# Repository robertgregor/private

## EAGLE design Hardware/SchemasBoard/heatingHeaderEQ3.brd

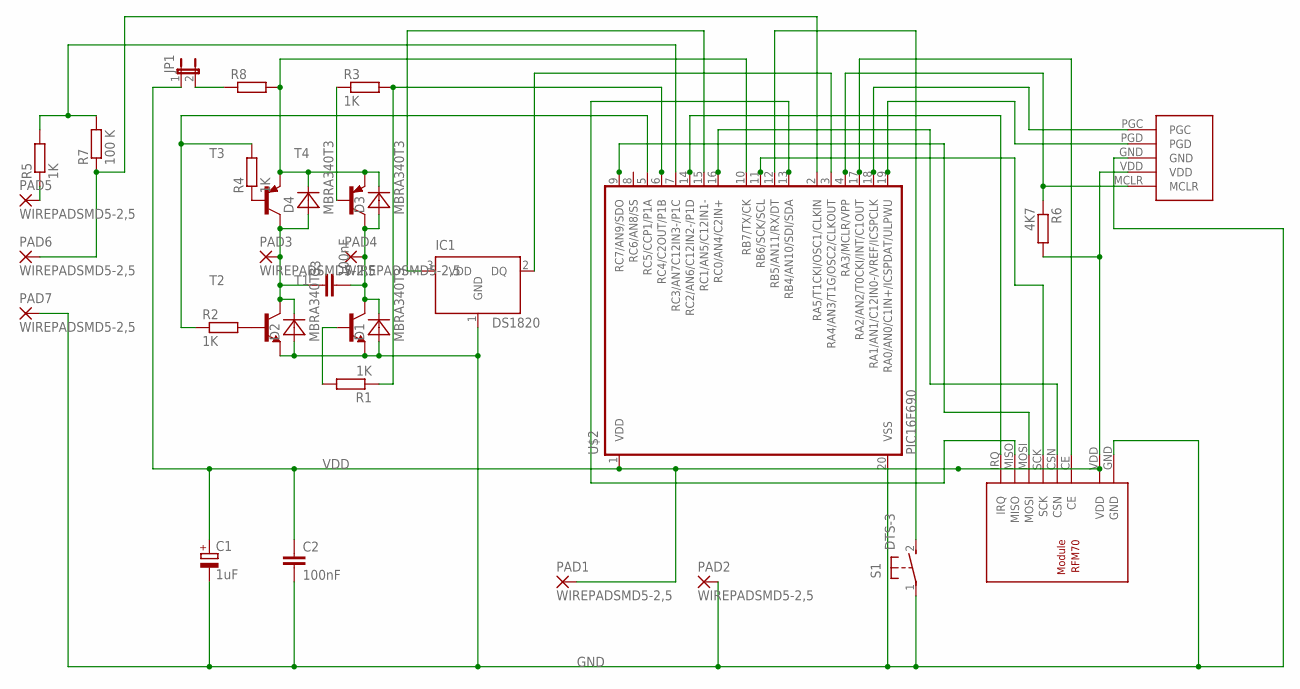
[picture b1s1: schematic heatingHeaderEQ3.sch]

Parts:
C1: 1uF; SMC_A
C2, C3: 100nF; C2012
D1, D2, D3, D4: MBRA340T3; SMA
IC1: DS1820; TO-92
JP1: JP1E; JP1
PAD1, PAD2, PAD3, PAD4, PAD5, PAD6, PAD7: WIREPADSMD5-2,5; 5-2,5
R1, R2, R3, R4, R5: 1K; R1206
R6: 4K7; R1206W
R7: 100 K; R1206
R8: R-EU_R2512W; R2512W
S1: DTS-3
T1, T2: BC817-40-NPN-SOT23-BEC; SOT23-BEC
T3, T4: BC807-16-PNP-SOT23-BEC; SOT23-BEC
U$1: RFM70
U$2: PIC16F690; SSOP20
U$3: PROGRAMMINGHEADERDIP; PROGHEADER

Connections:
GND: C1.-, C2.2, D1.A, D2.A, IC1.1 (GND), PAD2.1, PAD7.1, S1.1, T1.E, T2.E, U$1.GND, U$2.20 (VSS), U$3.GND
unnamed: IC1.2 (DQ), U$2.3 (RA4/AN3/T1G/OSC2/CLKOUT)
unnamed: JP1.2, R8.1
unnamed: IC1.3 (VDD), U$2.15 (RC1/AN5/C12IN1-)
unnamed: PAD5.1, R5.1
unnamed: U$1.MISO, U$2.13 (RB4/AN10/SDI/SDA)
unnamed: C3.1, D2.C, D4.A, PAD3.1, T2.C, T3.C
unnamed: C3.2, D1.C, D3.A, PAD4.1, T1.C, T4.C
unnamed: PAD6.1, R7.1, U$2.2 (RA5/T1CKI/OSC1/CLKIN)
unnamed: S1.2, U$2.12 (RB5/AN11/RX/DT)
unnamed: R5.2, R7.2, U$2.7 (RC3/AN7C12IN3-/P1C)
unnamed: R2.2, T2.B
unnamed: R4.1, T3.B
unnamed: D3.C, D4.C, R8.2, T3.E, T4.E, U$2.10 (RB7/TX/CK)
unnamed: U$1.CE, U$2.17 (RA2/AN2/T0CKI/INT/C1OUT)
unnamed: U$2.19 (RA0/AN0/C1IN+/ICSPDAT/ULPWU), U$3.PGD
unnamed: U$2.18 (RA1/AN1/C12IN0-/VREF/ICSPCLK), U$3.PGC
unnamed: U$1.CSN, U$2.16 (RC0/AN4/C2IN+)
unnamed: U$1.IRQ, U$2.14 (RC2/AN6/C12IN2-/P1D)
unnamed: U$1.SCK, U$2.11 (RB6/SCK/SCL)
unnamed: U$1.MOSI, U$2.9 (RC7/AN9/SDO)
unnamed: R1.2, T1.B
unnamed: R6.1, U$2.4 (RA3/MCLR/VPP), U$3.MCLR
unnamed: R3.1, T4.B
unnamed: R1.1, R3.2, U$2.6 (RC4/C2OUT/P1B)
unnamed: R2.1, R4.2, U$2.5 (RC5/CCP1/P1A)
VDD: C1.+, C2.1, JP1.1, PAD1.1, R6.2, U$1.VDD, U$2.1 (VDD), U$3.VDD

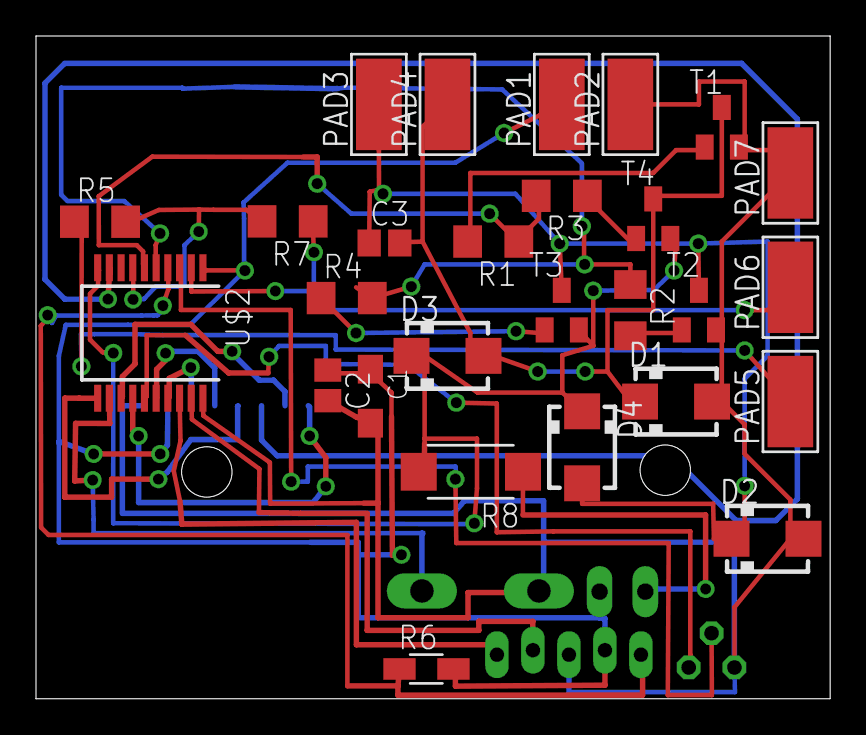
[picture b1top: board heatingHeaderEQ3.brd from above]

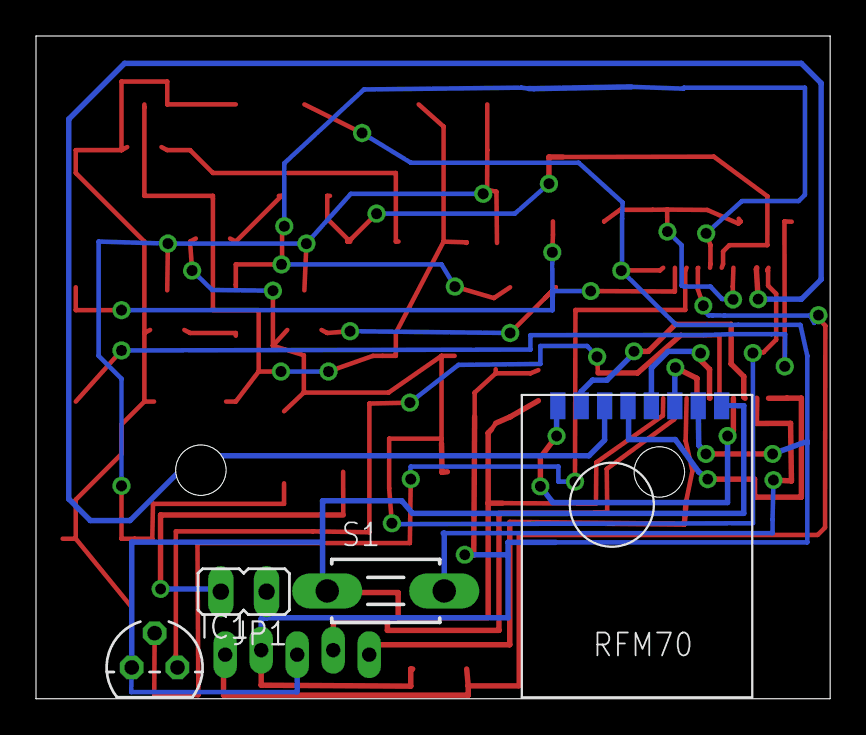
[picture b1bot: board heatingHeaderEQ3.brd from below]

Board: 2 copper layers, 44.1 x 36.8 mm, 32 parts (5 on the bottom side), 27 nets.

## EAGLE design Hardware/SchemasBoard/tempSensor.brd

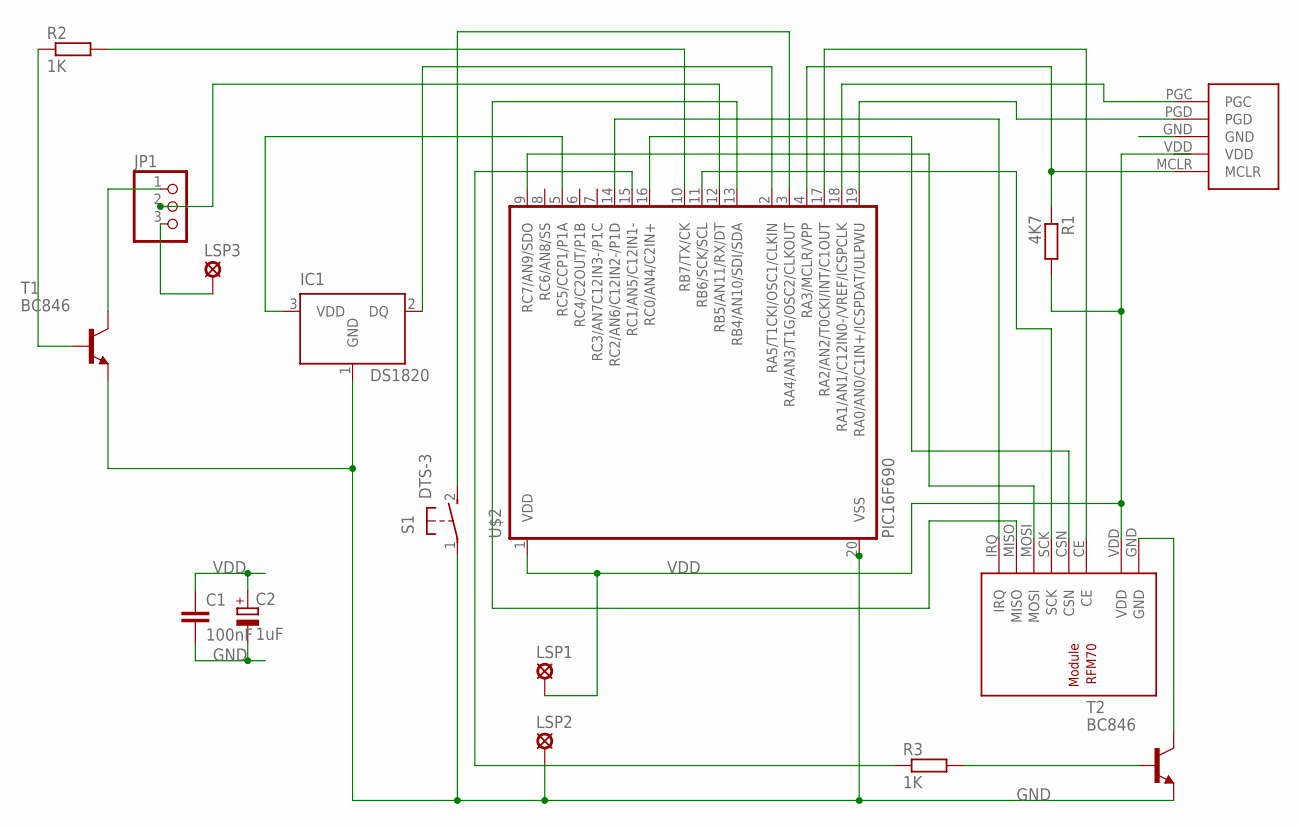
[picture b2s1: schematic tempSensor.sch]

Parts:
C1: 100nF; C2012
C2: 1uF; SMC_A
IC1: DS1820; TO-92
JP1: PINHD-1X3; 1X03
LSP1, LSP2, LSP3: SE14
R1: 4K7; R1206W
R2, R3: 1K; R1206W
S1: DTS-3
T1, T2: BC846; SOT23
U$1: RFM70
U$2: PIC16F690; SSOP20
U$3: PROGRAMMINGHEADERDIP; PROGHEADER

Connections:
GND: C1.2, C2.-, IC1.1 (GND), LSP2.MP, S1.1, T1.2 (E), T2.2 (E), U$2.20 (VSS)
unnamed: IC1.2 (DQ), U$2.2 (RA5/T1CKI/OSC1/CLKIN)
unnamed: S1.2, U$2.3 (RA4/AN3/T1G/OSC2/CLKOUT)
unnamed: IC1.3 (VDD), U$2.5 (RC5/CCP1/P1A)
unnamed: JP1.2, U$2.12 (RB5/AN11/RX/DT)
unnamed: JP1.3, LSP3.MP
unnamed: R2.2, U$2.10 (RB7/TX/CK)
unnamed: R2.1, T1.1 (B)
unnamed: U$2.19 (RA0/AN0/C1IN+/ICSPDAT/ULPWU), U$3.PGD
unnamed: JP1.1, T1.3 (C)
unnamed: U$2.18 (RA1/AN1/C12IN0-/VREF/ICSPCLK), U$3.PGC
unnamed: U$1.MISO, U$2.13 (RB4/AN10/SDI/SDA)
unnamed: T2.3 (C), U$1.GND
unnamed: R3.2, T2.1 (B)
unnamed: R3.1, U$2.15 (RC1/AN5/C12IN1-)
unnamed: U$1.CE, U$2.17 (RA2/AN2/T0CKI/INT/C1OUT)
unnamed: U$1.CSN, U$2.16 (RC0/AN4/C2IN+)
unnamed: U$1.IRQ, U$2.14 (RC2/AN6/C12IN2-/P1D)
unnamed: U$1.SCK, U$2.11 (RB6/SCK/SCL)
unnamed: U$1.MOSI, U$2.9 (RC7/AN9/SDO)
unnamed: R1.1, U$2.4 (RA3/MCLR/VPP), U$3.MCLR
VDD: C1.1, C2.+, LSP1.MP, R1.2, U$1.VDD, U$2.1 (VDD), U$3.VDD

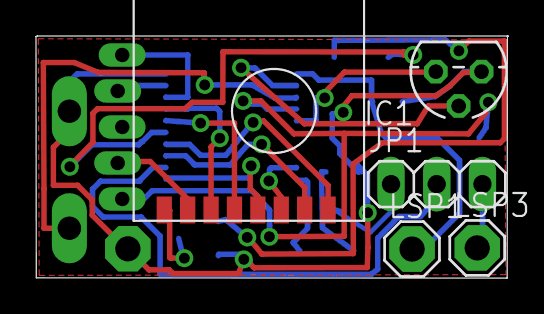
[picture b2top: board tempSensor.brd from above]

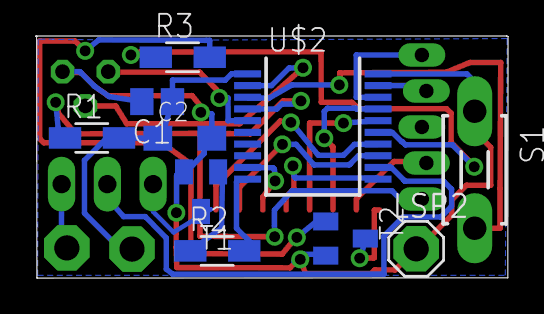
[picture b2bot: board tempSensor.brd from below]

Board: 2 copper layers, 26.2 x 13.4 mm, 16 parts (10 on the bottom side), 22 nets.
